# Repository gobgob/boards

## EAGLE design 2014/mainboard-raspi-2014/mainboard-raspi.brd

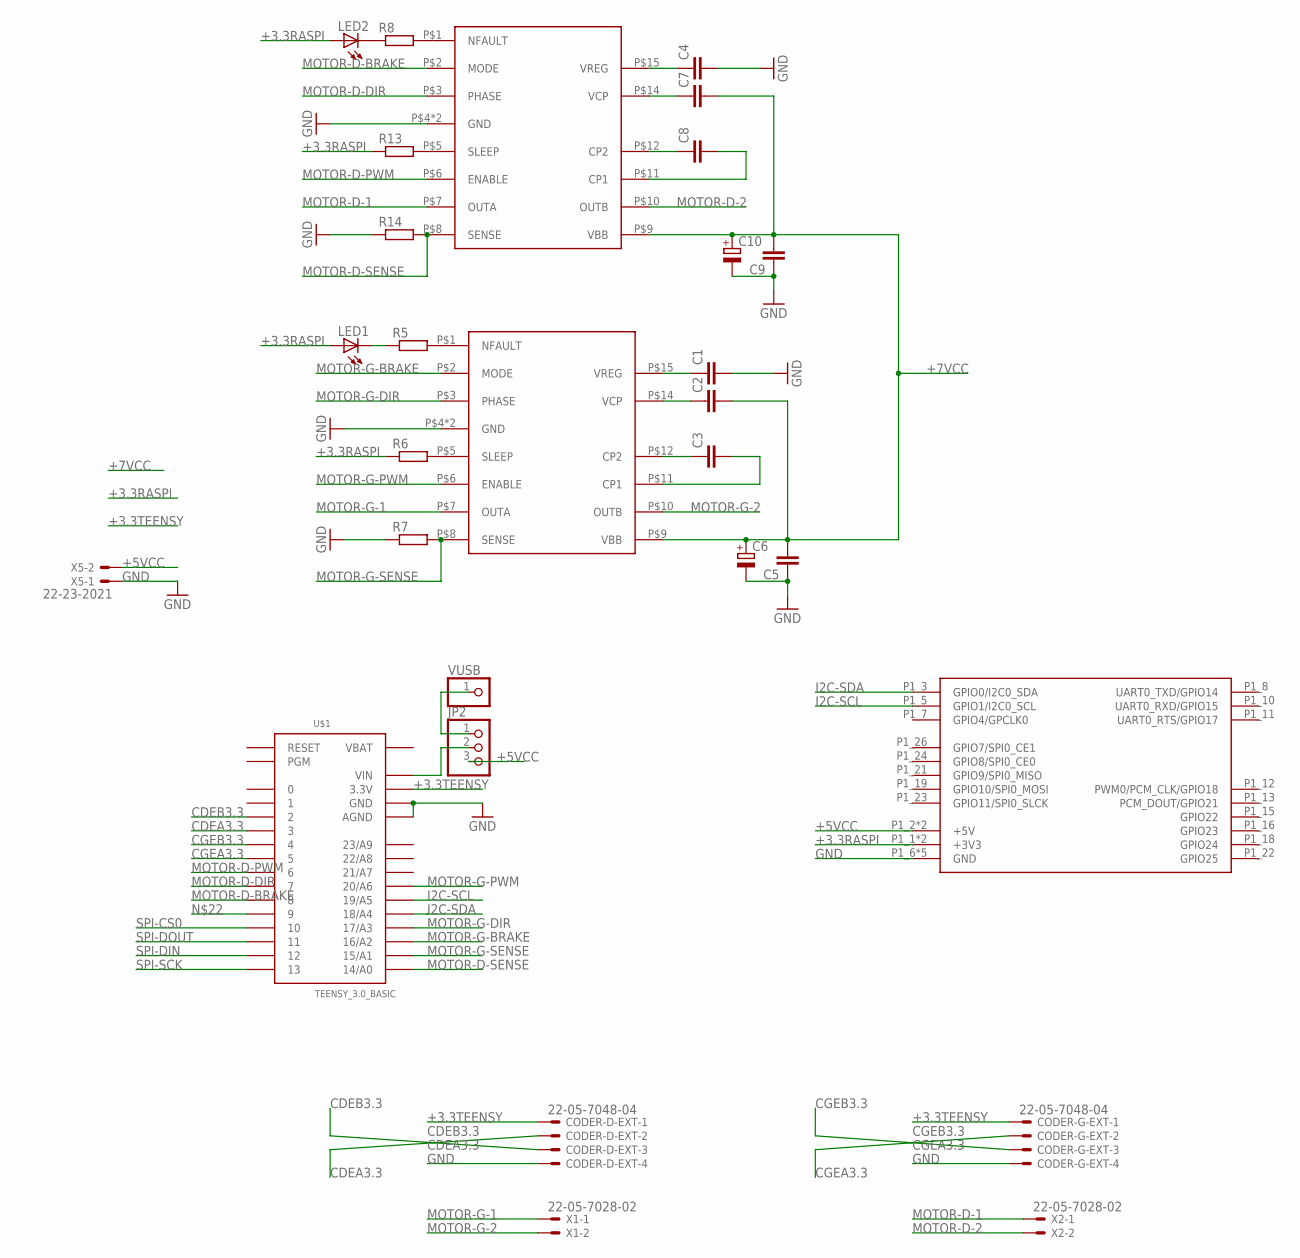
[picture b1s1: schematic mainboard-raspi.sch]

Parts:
C1, C2, C3, C4, C5, C7, C8, C9: C-EUC0805K; C0805K
C6, C10: CPOL-EUE3.5-8; E3,5-8
CODER-D-EXT: 22-05-7048-04; 7395-04
CODER-G-EXT: 22-05-7048-04; 7395-04
JP2: PINHD-1X3; 1X03
LED1, LED2: LED3MM
R5, R6, R7, R8, R13, R14: R-EU_R0805W; R0805W
U$1: TEENSY_3.0_BASIC
U$3, U$4: A3950-DIL; DIL16
U$5: RPI-B-V1SHIELD; RPI-B-V1-SHIELD
VUSB: PINHD-1X1; 1X01
X1, X2: 22-05-7028-02; 7395-02
X5: 22-23-2021

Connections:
+3.3RASPI: LED1.A, LED2.A, R6.1, R13.1, U$5.P1_1 (+3V3), U$5.P1_17 (+3V3)
+3.3TEENSY: CODER-D-EXT.1, CODER-G-EXT.1, U$1.3.3V, U$1.3.3V1 (3.3V)
+5VCC: JP2.3, U$5.P1_2 (+5V), U$5.P1_4 (+5V), X5.2
+7VCC: C2.2, C5.2, C6.+, C7.2, C9.2, C10.+, U$3.P$9 (VBB), U$4.P$9 (VBB)
CDEA3.3: CODER-D-EXT.2, U$1.3
CDEB3.3: CODER-D-EXT.3, U$1.2
CGEA3.3: CODER-G-EXT.2, U$1.5
CGEB3.3: CODER-G-EXT.3, U$1.4
GND: C1.2, C4.2, C5.1, C6.-, C9.1, C10.-, CODER-D-EXT.4, CODER-G-EXT.4, R7.1, R14.1, U$1.AGND, U$1.GND, U$1.GND1 (GND), U$3.P$4 (GND), U$3.P$13 (GND), U$4.P$4 (GND), U$4.P$13 (GND), U$5.P1_6 (GND), U$5.P1_9 (GND), U$5.P1_14 (GND), U$5.P1_20 (GND), U$5.P1_25 (GND), X5.1
I2C-SCL: U$1.19/A5, U$5.P1_5 (GPIO1/I2C0_SCL)
I2C-SDA: U$1.18/A4, U$5.P1_3 (GPIO0/I2C0_SDA)
MOTOR-D-1: U$4.P$7 (OUTA), X2.1
MOTOR-D-2: U$4.P$10 (OUTB), X2.2
MOTOR-D-BRAKE: U$1.8, U$4.P$2 (MODE)
MOTOR-D-DIR: U$1.7, U$4.P$3 (PHASE)
MOTOR-D-PWM: U$1.6, U$4.P$6 (ENABLE)
MOTOR-D-SENSE: R14.2, U$1.14/A0, U$4.P$8 (SENSE)
MOTOR-G-1: U$3.P$7 (OUTA), X1.1
MOTOR-G-2: U$3.P$10 (OUTB), X1.2
MOTOR-G-BRAKE: U$1.16/A2, U$3.P$2 (MODE)
MOTOR-G-DIR: U$1.17/A3, U$3.P$3 (PHASE)
MOTOR-G-PWM: U$1.20/A6, U$3.P$6 (ENABLE)
MOTOR-G-SENSE: R7.2, U$1.15/A1, U$3.P$8 (SENSE)
unnamed: JP2.2, U$1.VIN
unnamed: JP2.1, VUSB.1
unnamed: R5.2, U$3.P$1 (NFAULT)
unnamed: R6.2, U$3.P$5 (SLEEP)
unnamed: R8.2, U$4.P$1 (NFAULT)
unnamed: C1.1, U$3.P$15 (VREG)
unnamed: C2.1, U$3.P$14 (VCP)
unnamed: C3.1, U$3.P$12 (CP2)
unnamed: LED1.K (C), R5.1
unnamed: R13.2, U$4.P$5 (SLEEP)
unnamed: C4.1, U$4.P$15 (VREG)
unnamed: C7.1, U$4.P$14 (VCP)
unnamed: C3.2, U$3.P$11 (CP1)
unnamed: C8.1, U$4.P$12 (CP2)
unnamed: C8.2, U$4.P$11 (CP1)
unnamed: LED2.K (C), R8.1
SPI-CS0: U$1.10
SPI-DIN: U$1.12
SPI-DOUT: U$1.11
SPI-SCK: U$1.13
VBAT: U$1.VBAT

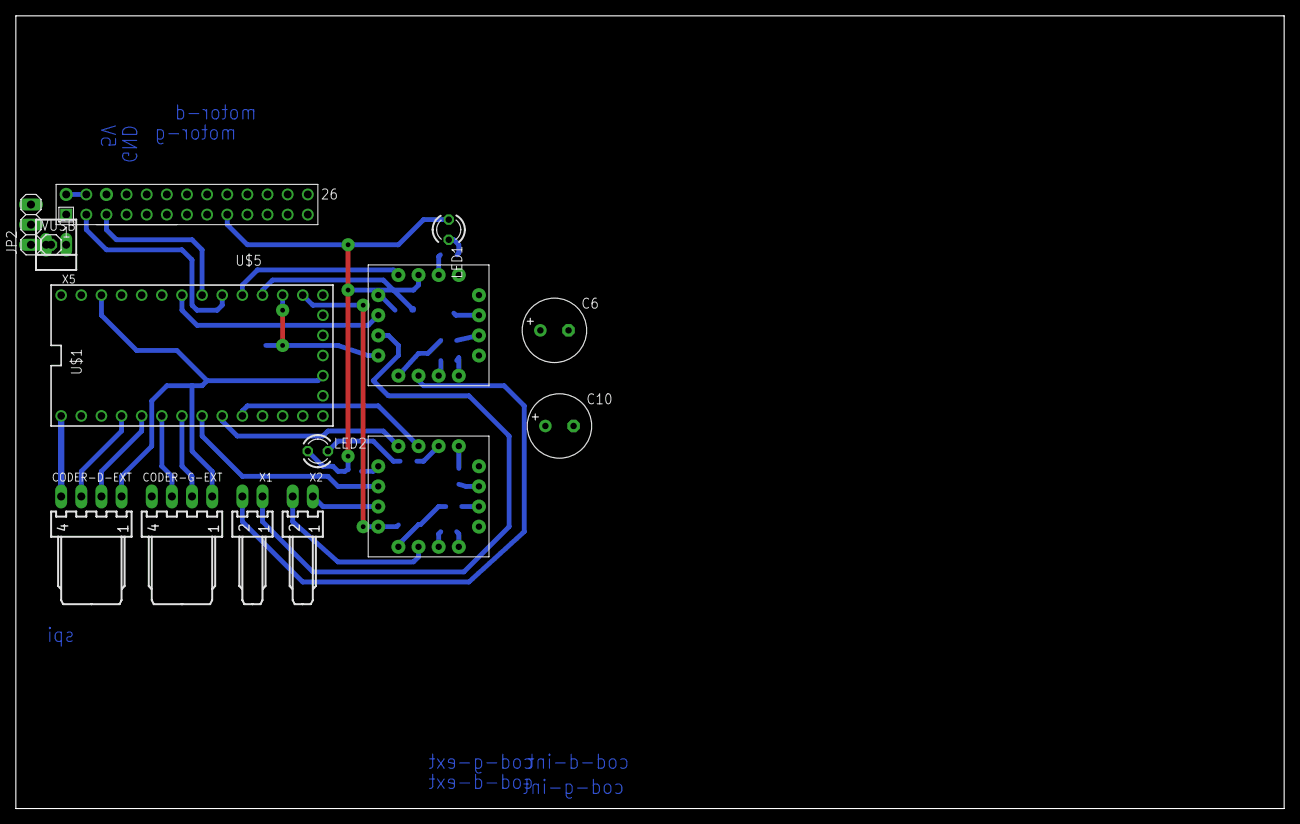
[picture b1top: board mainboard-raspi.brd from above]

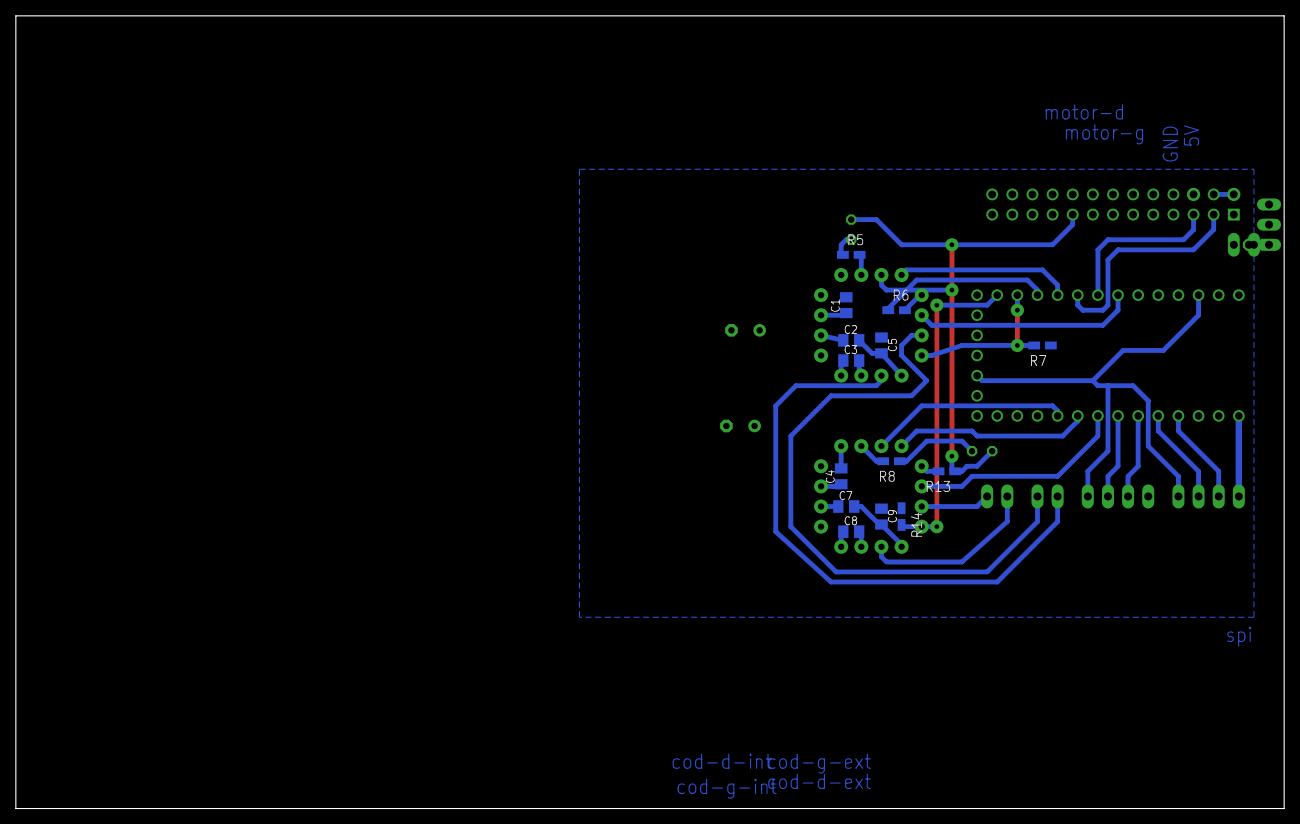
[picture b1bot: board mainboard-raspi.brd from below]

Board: 2 copper layers, 160.0 x 100.0 mm, 29 parts (14 on the bottom side), 39 nets.

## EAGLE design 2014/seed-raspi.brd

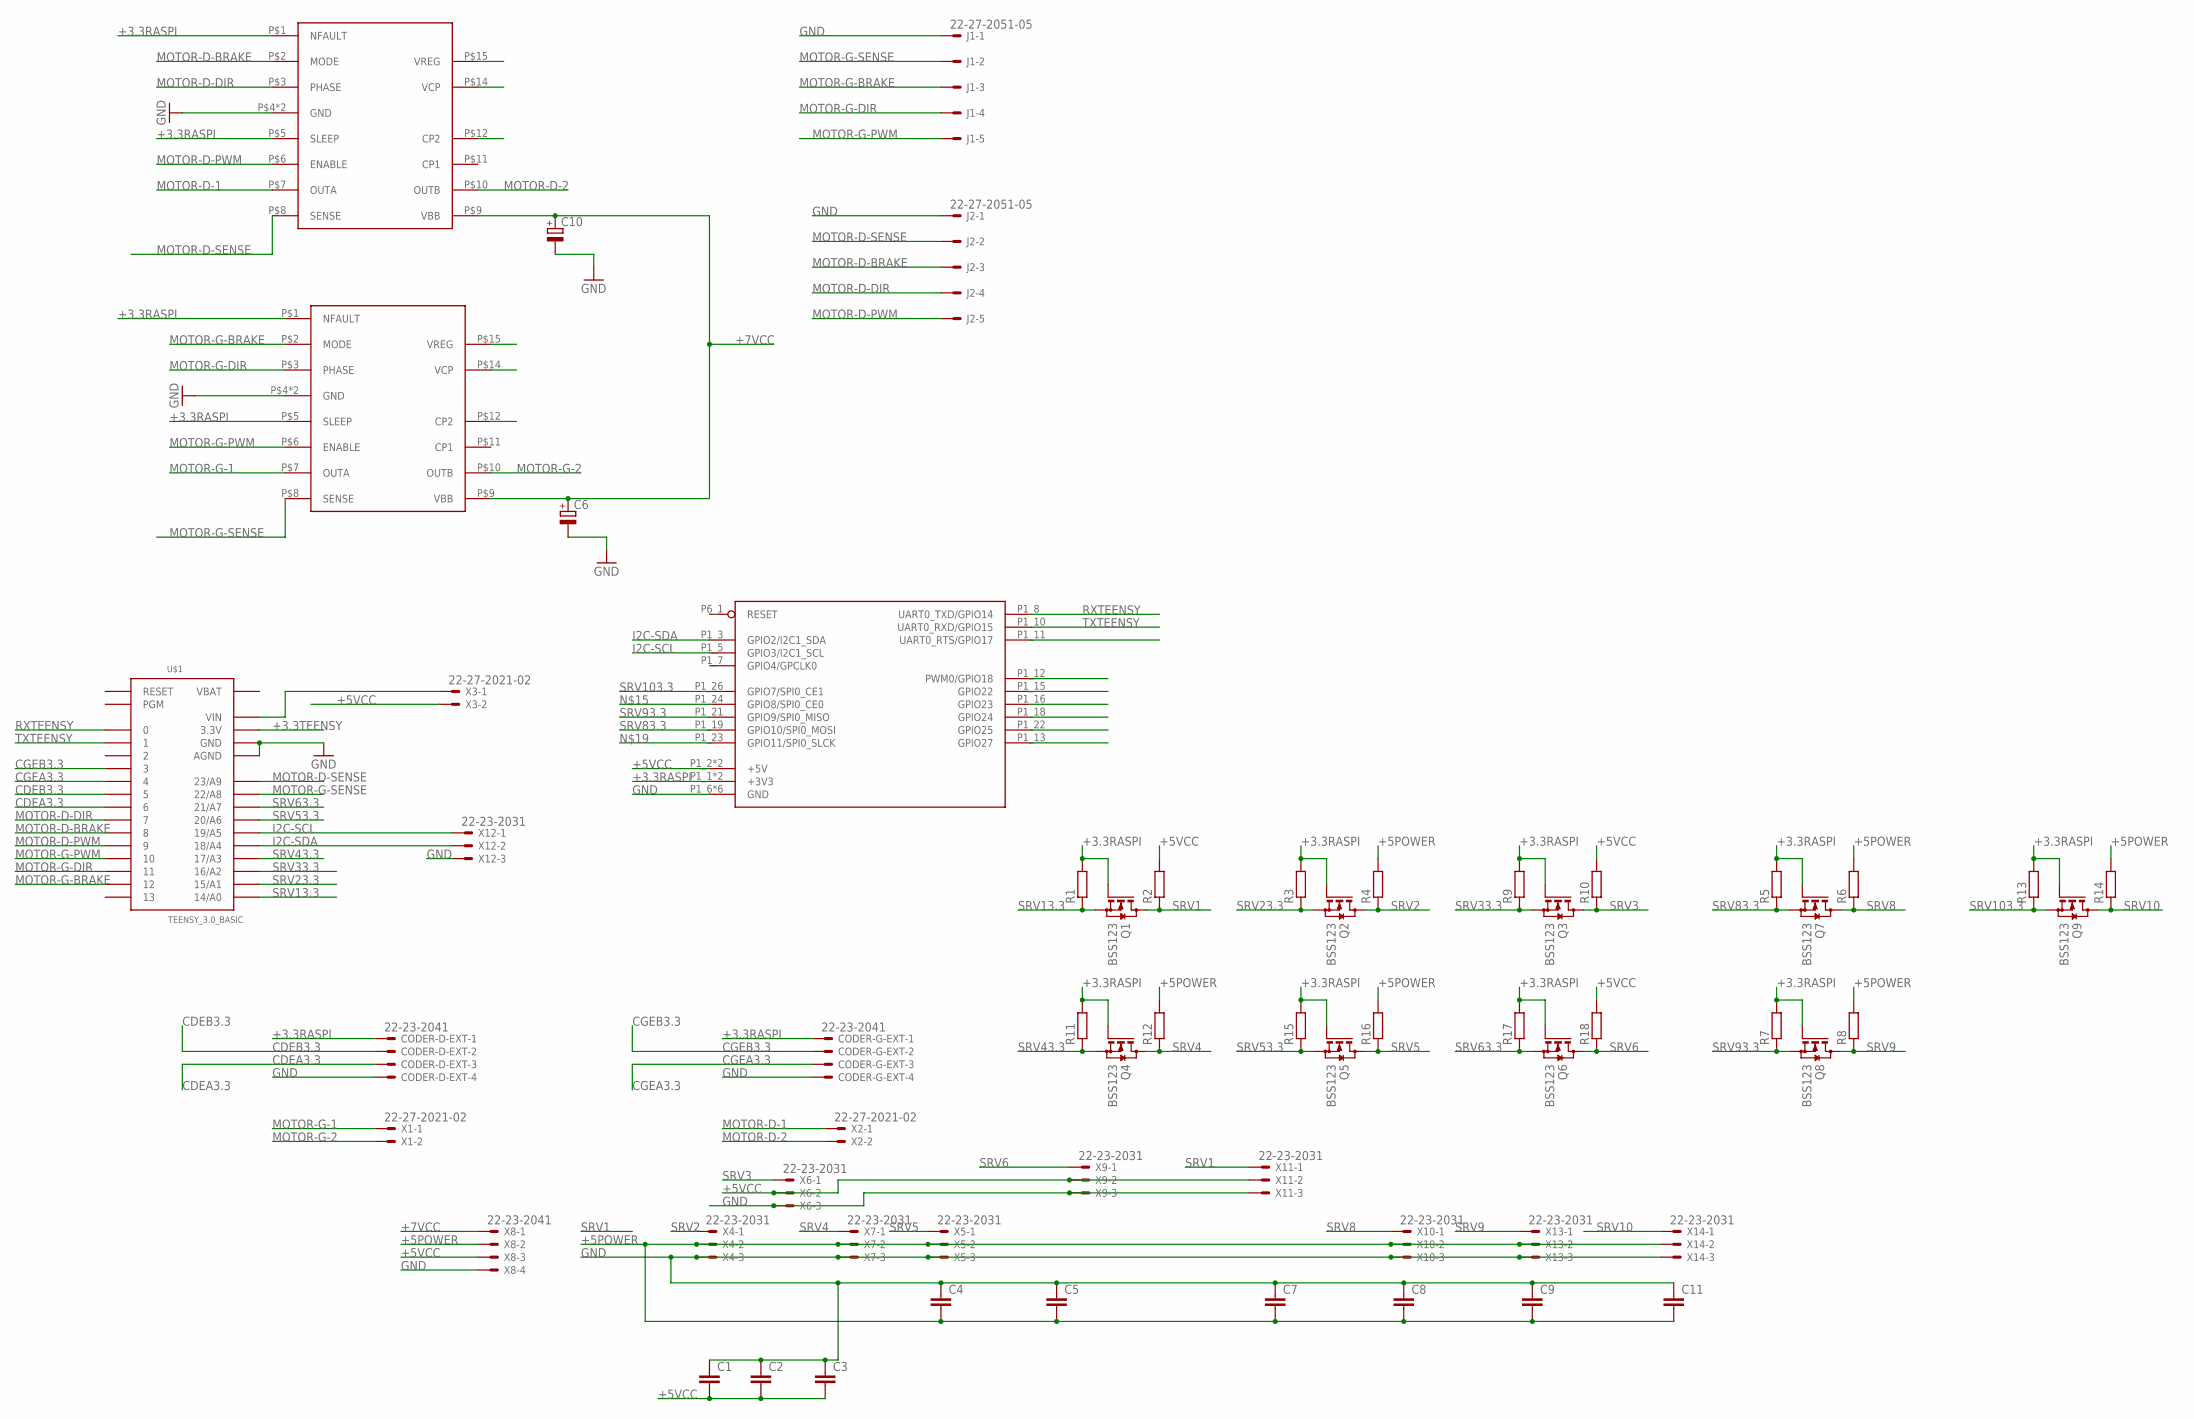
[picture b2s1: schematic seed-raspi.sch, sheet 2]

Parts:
C1, C2, C3, C4, C5, C7, C8, C9, C11: C-EUC0603K; C0603K
C6, C10: CPOL-EUE3.5-8; E3,5-8
CODER-D-EXT: 22-23-2041
CODER-G-EXT: 22-23-2041
J1, J2: 22-27-2051-05; 6410-05
Q1, Q2, Q3, Q4, Q5, Q6, Q7, Q8, Q9: BSS123; SOT23
R1, R2, R3, R4, R5, R6, R7, R8, R9, R10, R11, R12, R13, R14, R15, R16, R17, R18: R-EU_R0603; R0603
U$1: TEENSY_3.0_BASIC
U$2: RPI-B-V2SHIELD; RPI-B-V2-SHIELD
U$3, U$4: A3950-DIL; DIL16
X1, X2, X3: 22-27-2021-02; 6410-02
X4, X5, X6, X7, X9, X10, X11, X12, X13, X14: 22-23-2031
X8: 22-23-2041

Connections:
+3.3RASPI: CODER-D-EXT.1, CODER-G-EXT.1, Q1.1 (G), Q2.1 (G), Q3.1 (G), Q4.1 (G), Q5.1 (G), Q6.1 (G), Q7.1 (G), Q8.1 (G), Q9.1 (G), R1.2, R3.2, R5.2, R7.2, R9.2, R11.2, R13.2, R15.2, R17.2, U$2.P1_1 (+3V3), U$2.P1_17 (+3V3), U$3.P$1 (NFAULT), U$3.P$5 (SLEEP), U$4.P$1 (NFAULT), U$4.P$5 (SLEEP)
+3.3TEENSY: U$1.3.3V, U$1.3.3V1 (3.3V)
+5POWER: C4.2, C5.2, C7.2, C8.2, C9.2, C11.2, R4.2, R6.2, R8.2, R12.2, R14.2, R16.2, X4.2, X5.2, X7.2, X8.2, X10.2, X13.2, X14.2
+5VCC: C1.2, C2.2, C3.2, R2.2, R10.2, R18.2, U$2.P1_2 (+5V), U$2.P1_4 (+5V), X3.2, X6.2, X8.3, X9.2, X11.2
+7VCC: C6.+, C10.+, U$3.P$9 (VBB), U$4.P$9 (VBB), X8.1
CDEA3.3: CODER-D-EXT.3, U$1.6
CDEB3.3: CODER-D-EXT.2, U$1.5
CGEA3.3: CODER-G-EXT.3, U$1.4
CGEB3.3: CODER-G-EXT.2, U$1.3
GND: C1.1, C2.1, C3.1, C4.1, C5.1, C6.-, C7.1, C8.1, C9.1, C10.-, C11.1, CODER-D-EXT.4, CODER-G-EXT.4, J1.1, J2.1, U$1.AGND, U$1.GND, U$1.GND1 (GND), U$2.P1_6 (GND), U$2.P1_9 (GND), U$2.P1_14 (GND), U$2.P1_20 (GND), U$2.P1_25 (GND), U$2.P6_2 (GND), U$3.P$4 (GND), U$3.P$13 (GND), U$4.P$4 (GND), U$4.P$13 (GND), X4.3, X5.3, X6.3, X7.3, X8.4, X9.3, X10.3, X11.3, X12.3, X13.3, X14.3; also elsewhere on the board
I2C-SCL: U$1.19/A5, U$2.P1_5 (GPIO3/I2C1_SCL), X12.1
I2C-SDA: U$1.18/A4, U$2.P1_3 (GPIO2/I2C1_SDA), X12.2
MOTOR-D-1: U$4.P$7 (OUTA), X2.1
MOTOR-D-2: U$4.P$10 (OUTB), X2.2
MOTOR-D-BRAKE: J2.3, U$1.8, U$4.P$2 (MODE)
MOTOR-D-DIR: J2.4, U$1.7, U$4.P$3 (PHASE)
MOTOR-D-PWM: J2.5, U$1.9, U$4.P$6 (ENABLE)
MOTOR-D-SENSE: J2.2, U$1.23/A9, U$4.P$8 (SENSE)
MOTOR-G-1: U$3.P$7 (OUTA), X1.1
MOTOR-G-2: U$3.P$10 (OUTB), X1.2
MOTOR-G-BRAKE: J1.3, U$1.12, U$3.P$2 (MODE)
MOTOR-G-DIR: J1.4, U$1.11, U$3.P$3 (PHASE)
MOTOR-G-PWM: J1.5, U$1.10, U$3.P$6 (ENABLE)
MOTOR-G-SENSE: J1.2, U$1.22/A8, U$3.P$8 (SENSE)
unnamed: U$1.VIN, X3.1
RESET: U$2.P6_1 (RESET)
RXTEENSY: U$1.0, U$2.P1_8 (UART0_TXD/GPIO14)
SRV1: Q1.3 (D), R2.1, X11.1
SRV2: Q2.3 (D), R4.1, X4.1
SRV3: Q3.3 (D), R10.1, X6.1
SRV4: Q4.3 (D), R12.1, X7.1
SRV5: Q5.3 (D), R16.1, X5.1
SRV6: Q6.3 (D), R18.1, X9.1
SRV8: Q7.3 (D), R6.1, X10.1
SRV9: Q8.3 (D), R8.1, X13.1
SRV10: Q9.3 (D), R14.1, X14.1
SRV13.3: Q1.2 (S), R1.1, U$1.14/A0
SRV23.3: Q2.2 (S), R3.1, U$1.15/A1
SRV33.3: Q3.2 (S), R9.1, U$1.16/A2
SRV43.3: Q4.2 (S), R11.1, U$1.17/A3
SRV53.3: Q5.2 (S), R15.1, U$1.20/A6
SRV63.3: Q6.2 (S), R17.1, U$1.21/A7
SRV83.3: Q7.2 (S), R5.1, U$2.P1_19 (GPIO10/SPI0_MOSI)
SRV93.3: Q8.2 (S), R7.1, U$2.P1_21 (GPIO9/SPI0_MISO)
SRV103.3: Q9.2 (S), R13.1, U$2.P1_26 (GPIO7/SPI0_CE1)
TXTEENSY: U$1.1, U$2.P1_10 (UART0_RXD/GPIO15)
VBAT: U$1.VBAT

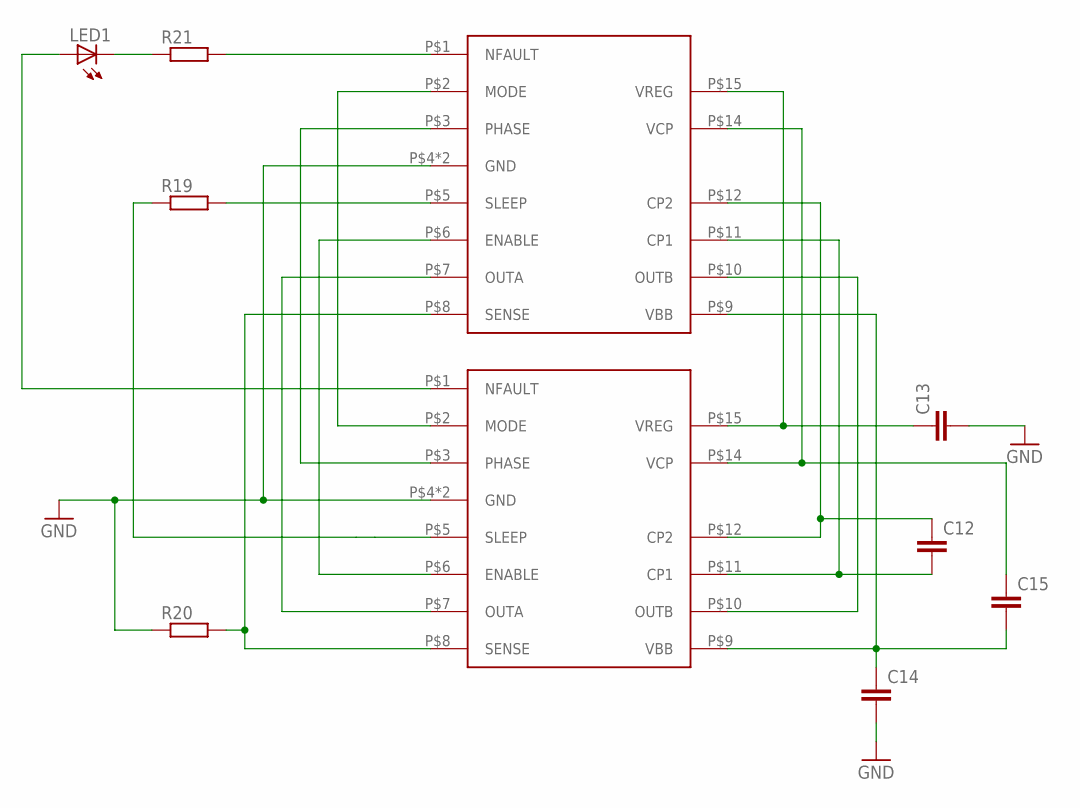
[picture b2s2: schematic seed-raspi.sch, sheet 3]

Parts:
C12, C13, C14, C15: C-EUC0603; C0603
LED1: LED3MM
R19, R20, R21: R-EU_R0603; R0603
U$5: A3950; 16TSSOP
U$6: A3950-DIL; DIL16

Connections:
GND: C13.2, C14.2, R20.1, U$5.P$4 (GND), U$5.P$13 (GND), U$6.P$4 (GND), U$6.P$13 (GND); also elsewhere on the board
unnamed: R19.1, U$6.P$5 (SLEEP)
unnamed: LED1.A, U$6.P$1 (NFAULT)
unnamed: U$5.P$2 (MODE), U$6.P$2 (MODE)
unnamed: U$5.P$3 (PHASE), U$6.P$3 (PHASE)
unnamed: U$5.P$6 (ENABLE), U$6.P$6 (ENABLE)
unnamed: U$5.P$7 (OUTA), U$6.P$7 (OUTA)
unnamed: R20.2, U$5.P$8 (SENSE), U$6.P$8 (SENSE)
unnamed: C13.1, U$5.P$15 (VREG), U$6.P$15 (VREG)
unnamed: C15.1, U$5.P$14 (VCP), U$6.P$14 (VCP)
unnamed: C12.1, U$5.P$12 (CP2), U$6.P$12 (CP2)
unnamed: C12.2, U$5.P$11 (CP1), U$6.P$11 (CP1)
unnamed: U$5.P$10 (OUTB), U$6.P$10 (OUTB)
unnamed: C14.1, C15.2, U$5.P$9 (VBB), U$6.P$9 (VBB)
unnamed: R19.2, U$5.P$5 (SLEEP)
unnamed: R21.2, U$5.P$1 (NFAULT)
unnamed: LED1.K (C), R21.1

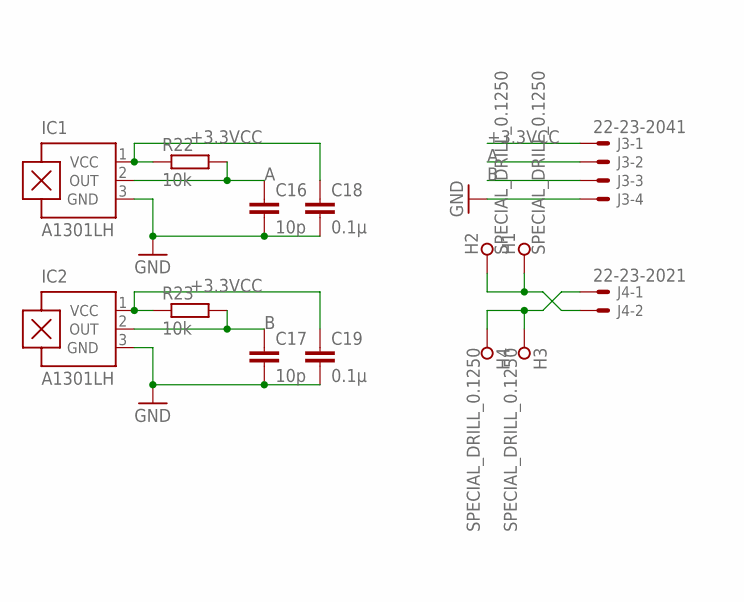
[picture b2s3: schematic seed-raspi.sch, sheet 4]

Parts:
C16, C17: 10p; C0805
C18, C19: 0.1µ; C0805
H1, H2, H3, H4: SPECIAL_DRILL_0.1250; PAD_0.1250
IC1, IC2: A1301LH; SOT23-W
J3: 22-23-2041
J4: 22-23-2021
R22, R23: 10k; R0805

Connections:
+3.3VCC: C18.1, C19.1, IC1.1 (VCC), IC2.1 (VCC), J3.1, R22.1, R23.1; also elsewhere on the board
A: C16.1, IC1.2 (OUT), J3.2, R22.2; also elsewhere on the board
B: C17.1, IC2.2 (OUT), J3.3, R23.2; also elsewhere on the board
GND: C16.2, C17.2, C18.2, C19.2, IC1.3 (GND), IC2.3 (GND), J3.4; also elsewhere on the board
unnamed: H1.1, H2.1, J4.2
unnamed: H3.1, H4.1, J4.1

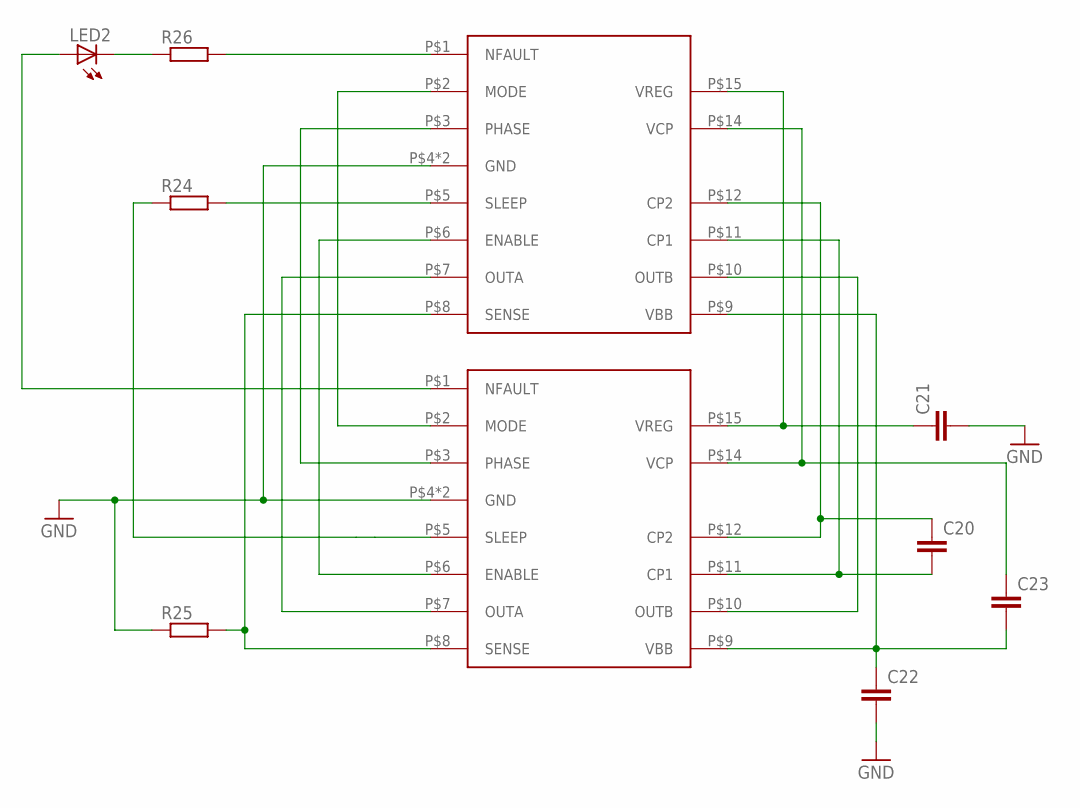
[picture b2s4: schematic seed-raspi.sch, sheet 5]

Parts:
C20, C21, C22, C23: C-EUC0603; C0603
LED2: LED3MM
R24, R25, R26: R-EU_R0603; R0603
U$7: A3950; 16TSSOP
U$8: A3950-DIL; DIL16

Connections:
GND: C21.2, C22.2, R25.1, U$7.P$4 (GND), U$7.P$13 (GND), U$8.P$4 (GND), U$8.P$13 (GND); also elsewhere on the board
unnamed: R24.1, U$8.P$5 (SLEEP)
unnamed: LED2.A, U$8.P$1 (NFAULT)
unnamed: U$7.P$2 (MODE), U$8.P$2 (MODE)
unnamed: U$7.P$3 (PHASE), U$8.P$3 (PHASE)
unnamed: U$7.P$6 (ENABLE), U$8.P$6 (ENABLE)
unnamed: U$7.P$7 (OUTA), U$8.P$7 (OUTA)
unnamed: R25.2, U$7.P$8 (SENSE), U$8.P$8 (SENSE)
unnamed: C21.1, U$7.P$15 (VREG), U$8.P$15 (VREG)
unnamed: C23.1, U$7.P$14 (VCP), U$8.P$14 (VCP)
unnamed: C20.1, U$7.P$12 (CP2), U$8.P$12 (CP2)
unnamed: C20.2, U$7.P$11 (CP1), U$8.P$11 (CP1)
unnamed: U$7.P$10 (OUTB), U$8.P$10 (OUTB)
unnamed: C22.1, C23.2, U$7.P$9 (VBB), U$8.P$9 (VBB)
unnamed: R24.2, U$7.P$5 (SLEEP)
unnamed: R26.2, U$7.P$1 (NFAULT)
unnamed: LED2.K (C), R26.1

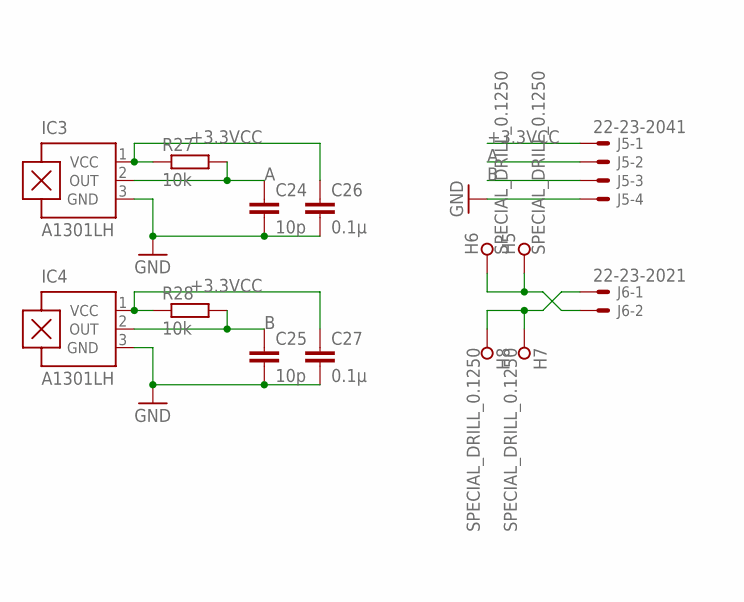
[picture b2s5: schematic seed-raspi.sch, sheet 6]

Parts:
C24, C25: 10p; C0805
C26, C27: 0.1µ; C0805
H5, H6, H7, H8: SPECIAL_DRILL_0.1250; PAD_0.1250
IC3, IC4: A1301LH; SOT23-W
J5: 22-23-2041
J6: 22-23-2021
R27, R28: 10k; R0805

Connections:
+3.3VCC: C26.1, C27.1, IC3.1 (VCC), IC4.1 (VCC), J5.1, R27.1, R28.1; also elsewhere on the board
A: C24.1, IC3.2 (OUT), J5.2, R27.2; also elsewhere on the board
B: C25.1, IC4.2 (OUT), J5.3, R28.2; also elsewhere on the board
GND: C24.2, C25.2, C26.2, C27.2, IC3.3 (GND), IC4.3 (GND), J5.4; also elsewhere on the board
unnamed: H5.1, H6.1, J6.2
unnamed: H7.1, H8.1, J6.1

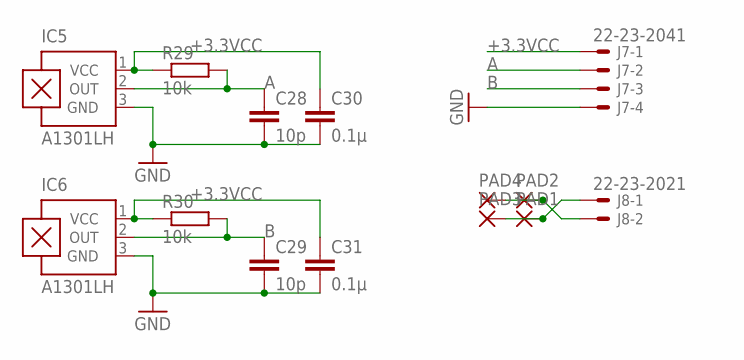
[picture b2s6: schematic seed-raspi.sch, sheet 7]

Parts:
C28, C29: 10p; C0805
C30, C31: 0.1µ; C0805
IC5, IC6: A1301LH; SOT23-W
J7: 22-23-2041
J8: 22-23-2021
PAD1, PAD2, PAD3, PAD4: 3,81/1,4
R29, R30: 10k; R0805

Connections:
+3.3VCC: C30.1, C31.1, IC5.1 (VCC), IC6.1 (VCC), J7.1, R29.1, R30.1; also elsewhere on the board
A: C28.1, IC5.2 (OUT), J7.2, R29.2; also elsewhere on the board
B: C29.1, IC6.2 (OUT), J7.3, R30.2; also elsewhere on the board
GND: C28.2, C29.2, C30.2, C31.2, IC5.3 (GND), IC6.3 (GND), J7.4; also elsewhere on the board
unnamed: J8.2, PAD2.1, PAD4.1
unnamed: J8.1, PAD1.1, PAD3.1

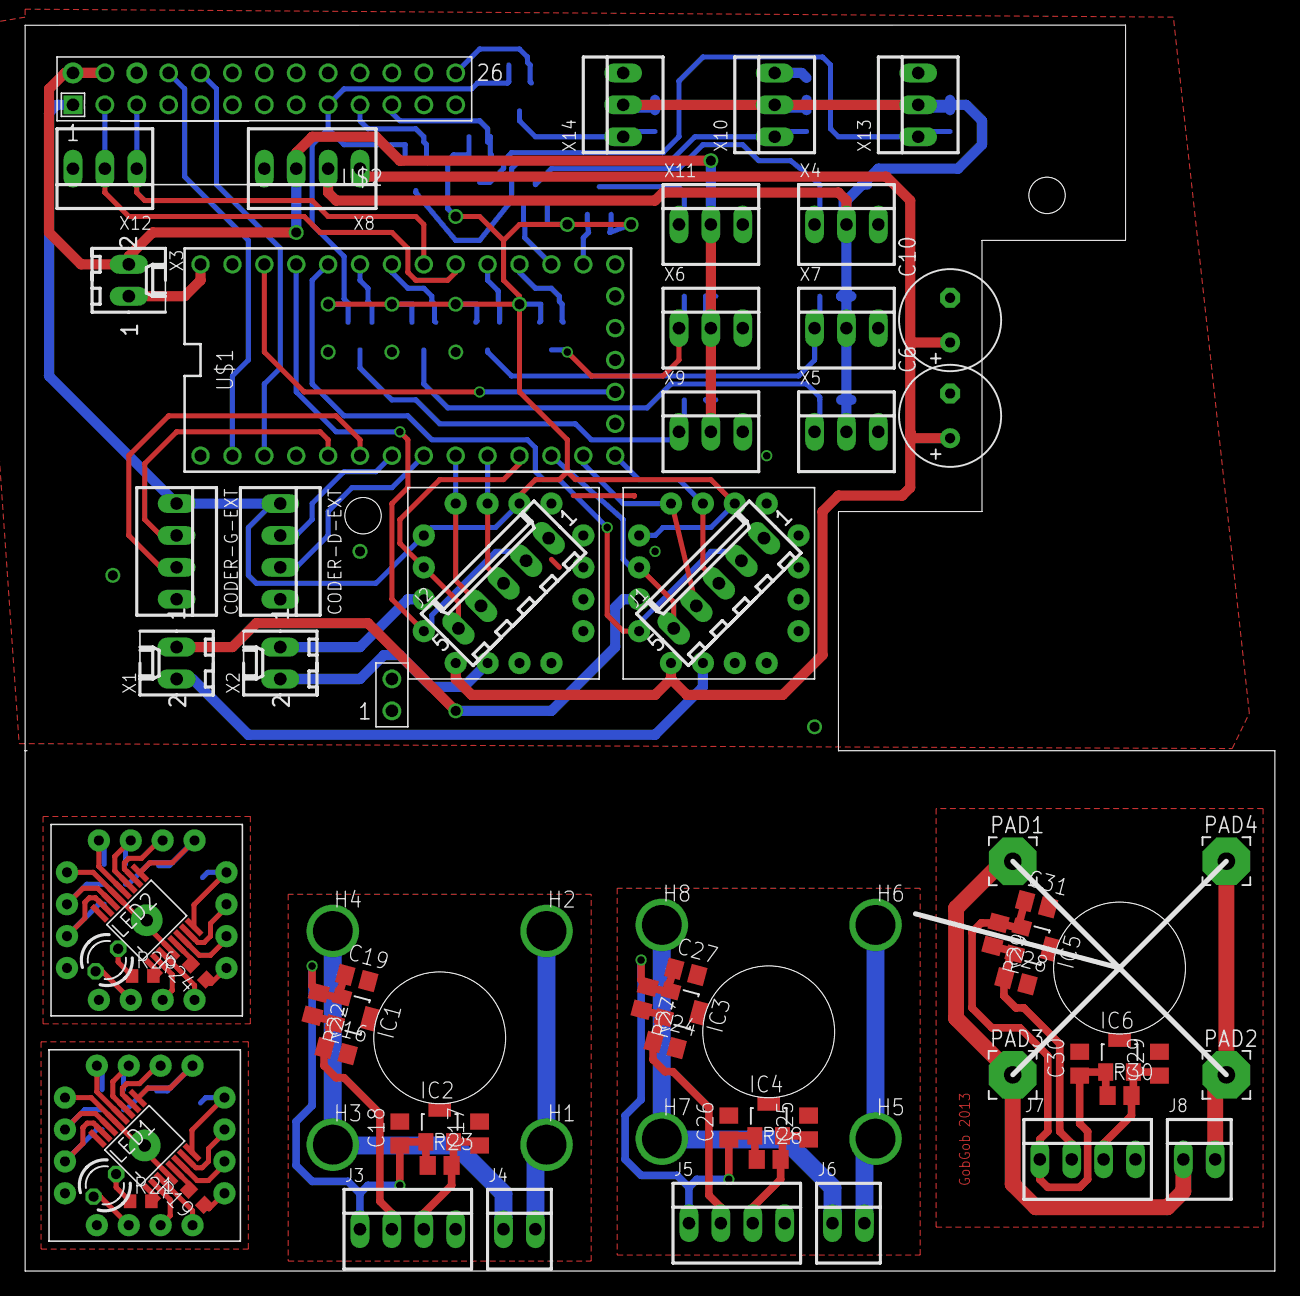
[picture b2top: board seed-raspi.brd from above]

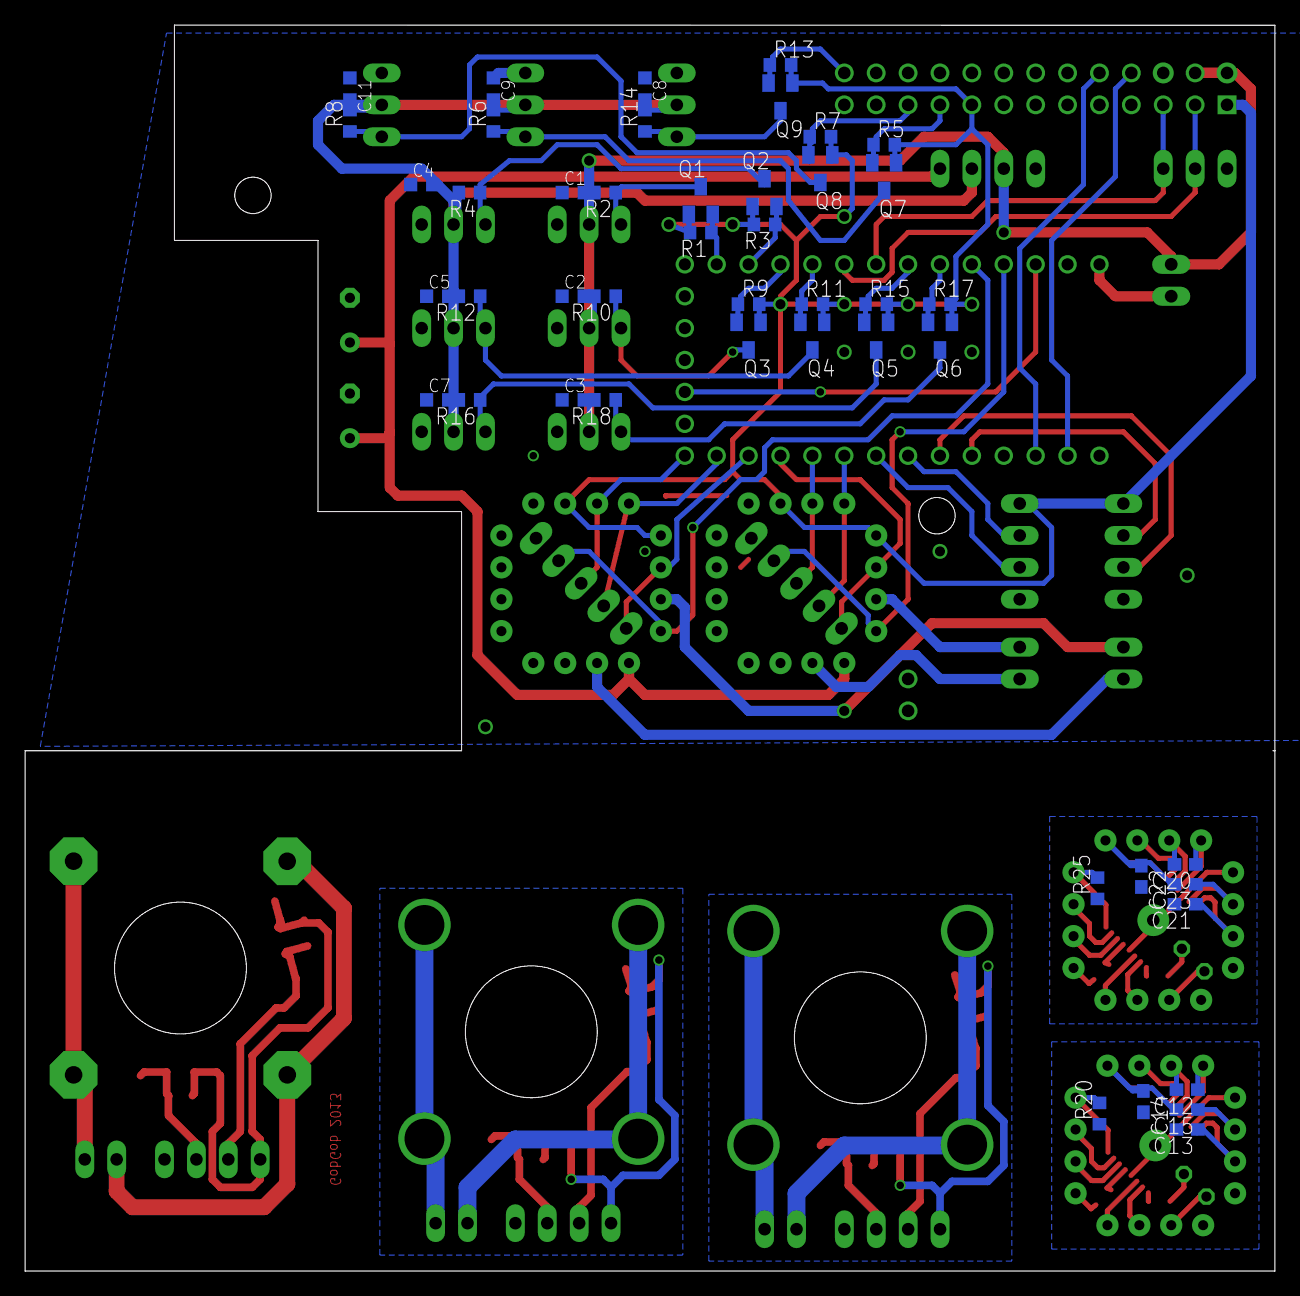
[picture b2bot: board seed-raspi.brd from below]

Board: 2 copper layers, 99.5 x 99.2 mm, 122 parts (46 on the bottom side), 86 nets.

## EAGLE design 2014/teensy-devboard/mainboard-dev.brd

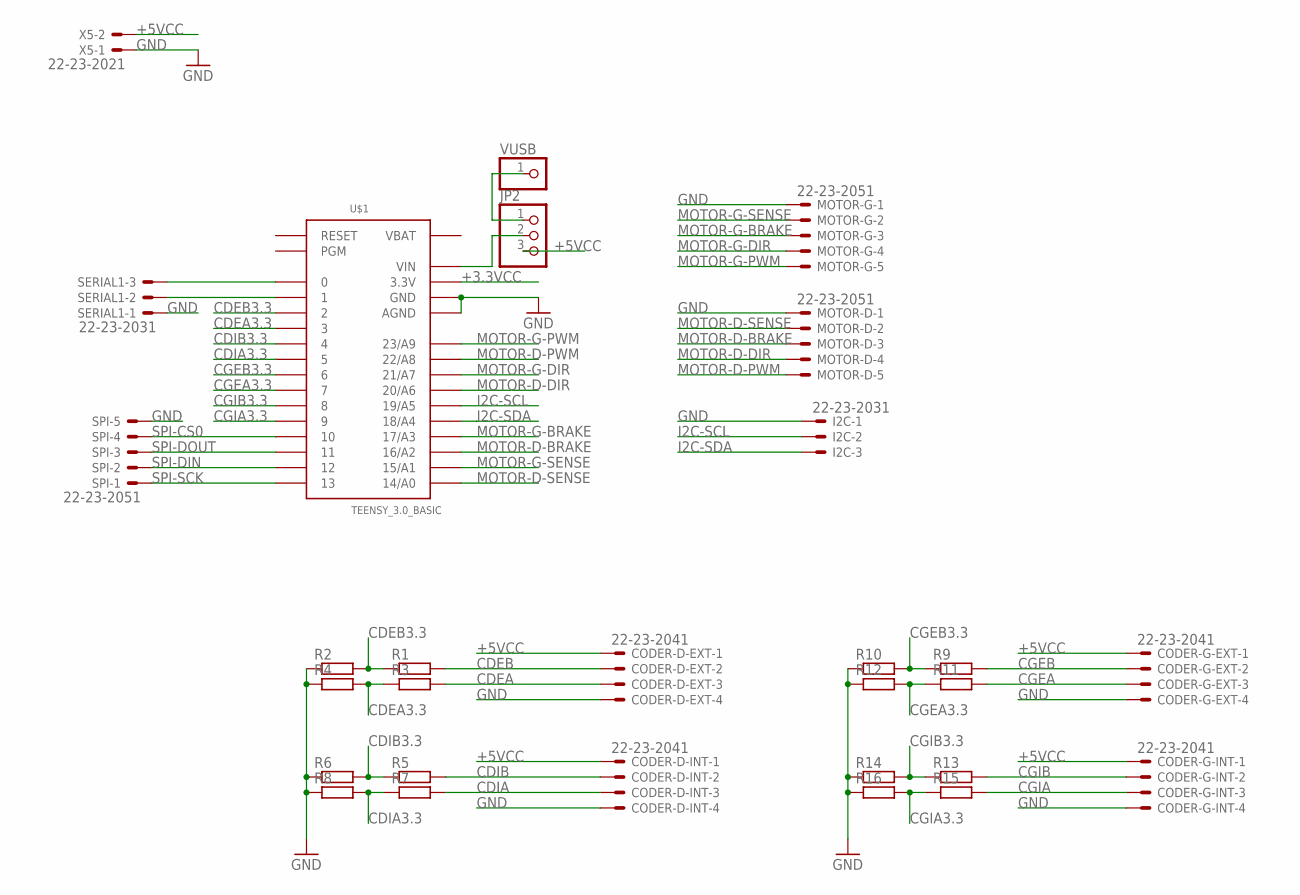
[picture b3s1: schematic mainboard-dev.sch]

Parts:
CODER-D-EXT: 22-23-2041
CODER-D-INT: 22-23-2041
CODER-G-EXT: 22-23-2041
CODER-G-INT: 22-23-2041
I2C: 22-23-2031
JP2: PINHD-1X3; 1X03
MOTOR-D: 22-23-2051
MOTOR-G: 22-23-2051
R1, R2, R3, R4, R5, R6, R7, R8, R9, R10, R11, R12, R13, R14, R15, R16: R-EU_0207/10; 0207/10
SERIAL1: 22-23-2031
SPI: 22-23-2051
U$1: TEENSY_3.0_BASIC
VUSB: PINHD-1X1; 1X01
X5: 22-23-2021

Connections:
+3.3VCC: U$1.3.3V, U$1.3.3V1 (3.3V)
+5VCC: CODER-D-EXT.1, CODER-D-INT.1, CODER-G-EXT.1, CODER-G-INT.1, JP2.3, X5.2
CDEA: CODER-D-EXT.3, R3.2
CDEA3.3: R3.1, R4.2, U$1.3
CDEB: CODER-D-EXT.2, R1.2
CDEB3.3: R1.1, R2.2, U$1.2
CDIA: CODER-D-INT.3, R7.2
CDIA3.3: R7.1, R8.2, U$1.5
CDIB: CODER-D-INT.2, R5.2
CDIB3.3: R5.1, R6.2, U$1.4
CGEA: CODER-G-EXT.3, R11.2
CGEA3.3: R11.1, R12.2, U$1.7
CGEB: CODER-G-EXT.2, R9.2
CGEB3.3: R9.1, R10.2, U$1.6
CGIA: CODER-G-INT.3, R15.2
CGIA3.3: R15.1, R16.2, U$1.9
CGIB: CODER-G-INT.2, R13.2
CGIB3.3: R13.1, R14.2, U$1.8
GND: CODER-D-EXT.4, CODER-D-INT.4, CODER-G-EXT.4, CODER-G-INT.4, I2C.1, MOTOR-D.1, MOTOR-G.1, R2.1, R4.1, R6.1, R8.1, R10.1, R12.1, R14.1, R16.1, SERIAL1.1, SPI.5, U$1.AGND, U$1.GND, U$1.GND1 (GND), X5.1
I2C-SCL: I2C.2, U$1.19/A5
I2C-SDA: I2C.3, U$1.18/A4
MOTOR-D-BRAKE: MOTOR-D.3, U$1.16/A2
MOTOR-D-DIR: MOTOR-D.4, U$1.20/A6
MOTOR-D-PWM: MOTOR-D.5, U$1.22/A8
MOTOR-D-SENSE: MOTOR-D.2, U$1.14/A0
MOTOR-G-BRAKE: MOTOR-G.3, U$1.17/A3
MOTOR-G-DIR: MOTOR-G.4, U$1.21/A7
MOTOR-G-PWM: MOTOR-G.5, U$1.23/A9
MOTOR-G-SENSE: MOTOR-G.2, U$1.15/A1
unnamed: SERIAL1.3, U$1.0
unnamed: SERIAL1.2, U$1.1
unnamed: JP2.2, U$1.VIN
unnamed: JP2.1, VUSB.1
SPI-CS0: SPI.4, U$1.10
SPI-DIN: SPI.2, U$1.12
SPI-DOUT: SPI.3, U$1.11
SPI-SCK: SPI.1, U$1.13
VBAT: U$1.VBAT

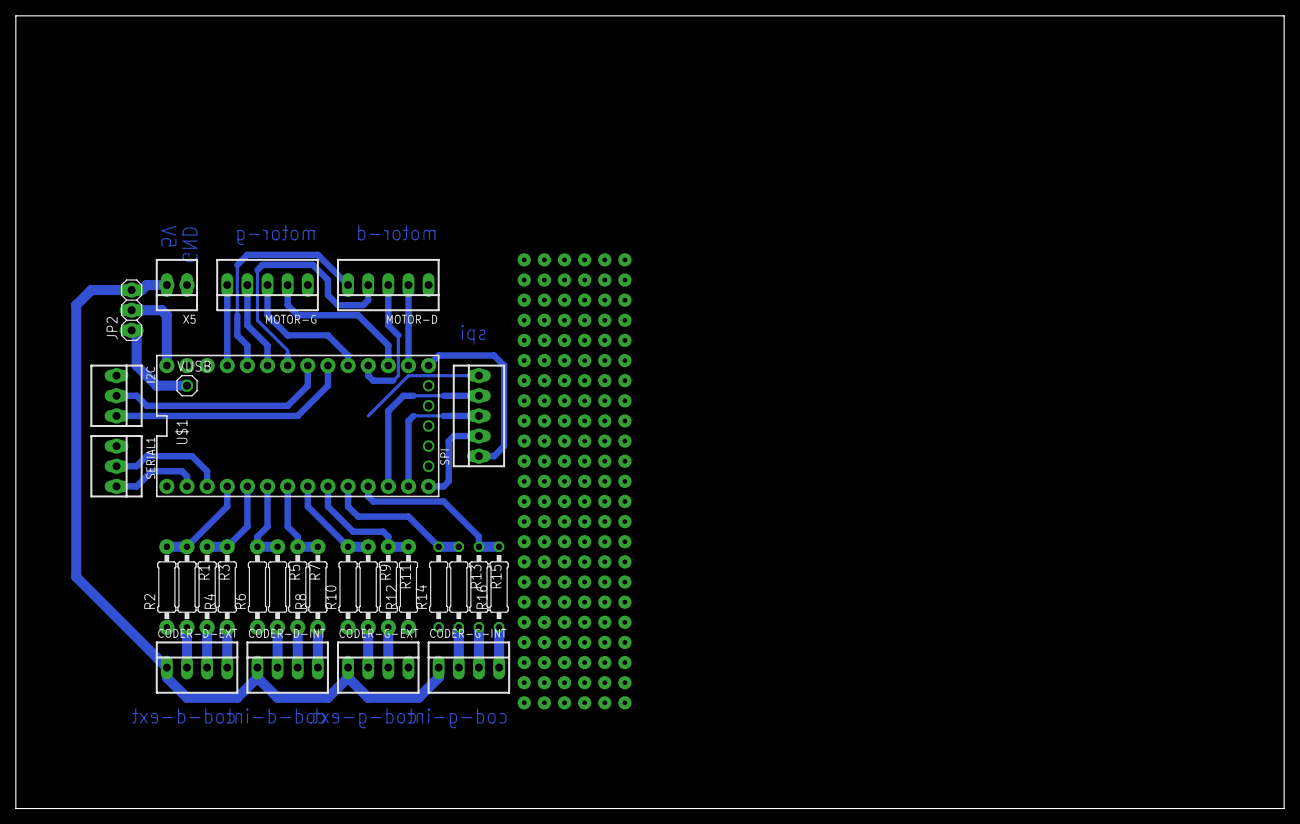
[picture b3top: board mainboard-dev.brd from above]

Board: 2 copper layers, 160.0 x 100.0 mm, 29 parts (0 on the bottom side), 37 nets.

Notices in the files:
parts and their libraries:
raspberry: This library stands under the CERN Open Hardware Licence.
SparkFun-LED: Licensing: Creative Commons ShareAlike 4.0 International - https://creativecommons.org/licenses/by-sa/4.0
